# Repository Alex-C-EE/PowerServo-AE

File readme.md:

_This entire project is currently a WIP by a single person, I aim to have a High-Power (12-24V @ 10A) and a Mid Power (6-24V @ 3.6A) version completely done by the end of the year 2024._

_**Really** open to contributors._

**_It would be a REALLY bad idea to try and manufacture anything present here at this time_**

**DCServo AE**

  DCServo AE is an open-source platform designed to effortlessly transform any Brushed DC motor into a continous smart servo with **high precision** and control. Built to provide **high-torque**, **high-RPM**, and accurate positioning through absolute encoding, DCServo AE is a modular solution for hobbyists, roboticists, and makers. 
  The platform allows users to easily drop in a PowerServo AE controller onto a brushed DC motor, turning it into a powerful and precise smart servo, regardless of the motor's size or specifications.

**Project Overview**

  The platform aims to support several variations, including options for high-power, low-power, high(er)-voltage, and low-voltage setups. Each variation is designed to accommodate different performance requirements while maintaining the core features of precise motion control and absolute position feedback. All variations will be based around the **STM32G0** series of microcontrollers due to their **low cost** and **powerful timers and peripherals**. Additionally, all versions will likely use **DRV-series drivers** to ensure robust motor control.

**Core Features**
- Plug and Play: With minimal considerations for design, it is ready to be strapped on the back of any **extended or dual axis/shaft, with magnet** BRUSHED DC Motor and turn it into a Smart Servo Motor.
- Absolute Encoder: PowerServo AE uses magnetic absolute encoders for precise positioning and reliable feedback, eliminating the need for homing or recalibration after power loss.
- Modular Design: Multiple configurations allow for flexibility across a wide range of applications, from lightweight robotics to heavy-duty industrial tasks.
- Open-Source: Both hardware and software are fully open-source, allowing anyone to contribute, modify, and improve the platform.
- Compact Size: The designs are optimized for compactness, with some controllers as small as 12 mm in diameter, making them suitable for space-constrained applications.

**Getting Started**

Clone the Repository:

``git clone https://github.com/Alex-C-EE/DCServo-AE.git``

**Build Your Own:**

- Design files (PCB, schematics) are provided in each version's hardware directory. Design files are in KiCad 8.0 format.
- Code (C, STM32) is provided in each version's software directory.
- GERBERS and BOMs are also provided ready to upload to JLCPCB.

**Documentation**

_WIP, planned control: CAN, UART, PWM_

**Contributing**

We welcome contributions to the PowerServo AE project! Whether you want to improve the hardware, add new features to the firmware, or suggest new variations, feel free to contribute through:

- Issues and Pull Requests on GitHub
- Community discussions in our Discord channel

**License**
- Hardware: Licensed under the CERN Open Hardware License.
- Software: Licensed under the MIT License.

**Join the Community**

_WIP_
Stay updated with the latest developments, tutorials, and community projects:

- Follow on Hackaday.io
- Join the discussion on Discord
- Watch video tutorials and project demos on YouTube

**Similar Projects (and source of inspiration)**

Mechaduino: Similar, but for Steppers specifically
https://hackaday.io/project/11224-mechaduino

MotCTRL: Similar, but for Brushless specifically
https://github.com/osannolik/MotCtrl

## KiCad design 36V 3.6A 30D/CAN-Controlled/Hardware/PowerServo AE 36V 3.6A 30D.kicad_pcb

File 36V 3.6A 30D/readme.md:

**TODO:**
- Ensure wider free area around mounting hole between CAN and XT30
- Open Solder Jumper for CAN
- Flip XT30 Gender Wise
- Round notch corners
- U2, C7, C8 orientation
- Pull Boot0 to ground (10k)
- Switch to DRV8521A
- Mousebite between data-line
  
**REMINDER**
- DO NOT USE FEROMAGNETIC STAND-OFF NEAR A SPINNING MAGNET AND A MAGNETOMETER

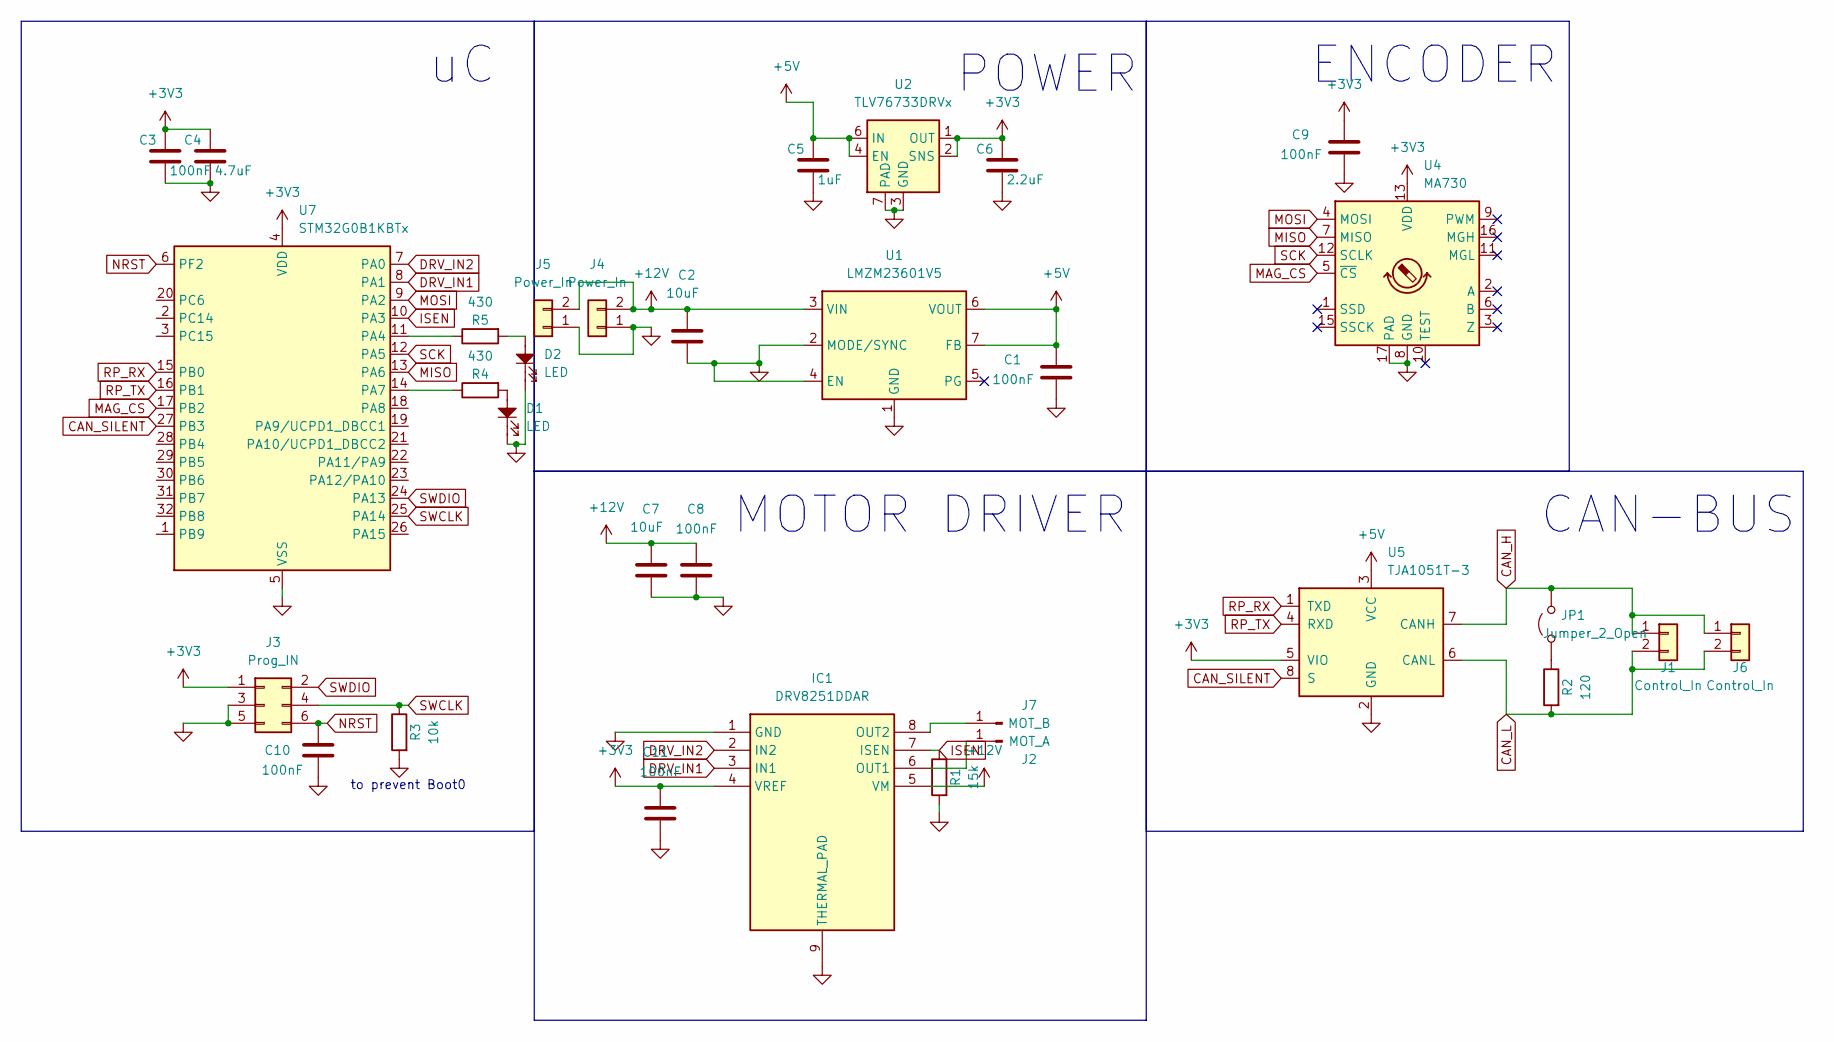
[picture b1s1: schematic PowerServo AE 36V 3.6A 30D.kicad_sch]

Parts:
C1, C3, C9, C10: 100nF; C_0402_1005Metric
C2, C7: 10uF; C_1206_3216Metric
C4: 4.7uF; C_0402_1005Metric
C5: 1uF; C_0402_1005Metric
C6: 2.2uF; C_0402_1005Metric
C8, C11: 100nF; C_0603_1608Metric
D1, D2: LED; LED_0402_1005Metric
IC1: DRV8251DDAR; SOIC127P600X170-9N; Mouser Part Number 595-DRV8251DDAR
J1, J6: Control_In; JST_XH_B2B-XH-A_1x02_P2.50mm_Vertical
J2: MOT_A; SolderWire-1sqmm_1x01_D1.4mm_OD2.7mm
J3: Prog_IN; PinHeader_2x03_P1.27mm_Vertical
J4, J5: Power_In; AMASS_XT30UPB-M_1x02_P5.0mm_Vertical
J7: MOT_B; SolderWire-1sqmm_1x01_D1.4mm_OD2.7mm
JP1: Jumper_2_Open; SolderJumper-2_P1.3mm_Open_Pad1.0x1.5mm
R1: 15k; R_0402_1005Metric
R2: 120; C_0402_1005Metric
R3: 10k; R_0402_1005Metric
R4, R5: 430; R_0402_1005Metric
U1: LMZM23601V5; Texas_SIL0010A_MicroSiP-10-1EP_3.8x3mm_P0.6mm_EP0.7x2.9mm_T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
U2: TLV76733DRVx; WSON-6-1EP_2x2mm_P0.65mm_EP1x1.6mm_ThermalVias
U4: MA730; QFN-16-1EP_3x3mm_P0.5mm_EP1.75x1.75mm
U5: TJA1051T-3; SOIC-8_3.9x4.9mm_P1.27mm
U7: STM32G0B1KBTx; LQFP-32_7x7mm_P0.8mm

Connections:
+3V3: C3.1, C4.1, C6.1, C9.2, C11.2, IC1.4 (VREF), J3.1, U2.1 (OUT), U2.2 (SNS), U4.13 (VDD), U5.5 (VIO), U7.4 (VDD)
+5V: C1.2, C5.1, U1.6 (VOUT), U1.7 (FB), U2.4 (EN), U2.6 (IN), U5.3 (VCC)
+12V: C2.2, C7.2, C8.2, IC1.5 (VM), J4.2, J5.2, U1.3 (VIN)
CAN_H: J1.1, J6.1, JP1.2 (B), U5.7 (CANH)
CAN_L: J1.2, J6.2, R2.2, U5.6 (CANL)
CAN_SILENT: U5.8 (S), U7.27 (PB3)
DRV_IN1: IC1.3 (IN1), U7.8 (PA1)
DRV_IN2: IC1.2 (IN2), U7.7 (PA0)
GND: C1.1, C2.1, C3.2, C4.2, C5.2, C6.2, C7.1, C8.1, C9.1, C10.1, C11.1, D1.1, D2.1, IC1.1 (GND), IC1.9 (THERMAL_PAD), J3.3, J3.5, J4.1, J5.1, R1.2, R3.2, U1.1 (GND), U1.2 (MODE/SYNC), U1.4 (EN), U1.11 (GND), U2.3 (GND), U2.5 (GND), U2.7 (PAD), U4.8 (GND), U4.17 (PAD), U5.2 (GND), U7.5 (VSS)
ISEN: IC1.7 (ISEN), R1.1, U7.10 (PA3)
MAG_CS: U4.5 (~CS), U7.17 (PB2)
MISO: U4.7 (MISO), U7.13 (PA6)
MOSI: U4.4 (MOSI), U7.9 (PA2)
NRST: C10.2, J3.6, U7.6 (PF2)
unnamed: D1.2, R4.2
unnamed: D2.2, R5.2
unnamed: IC1.6 (OUT1), J2.1
unnamed: IC1.8 (OUT2), J7.1
unnamed: JP1.1 (A), R2.1
unnamed: R5.1, U7.11 (PA4)
unnamed: R4.1, U7.14 (PA7)
RP_RX: U5.1 (TXD), U7.15 (PB0)
RP_TX: U5.4 (RXD), U7.16 (PB1)
SCK: U4.12 (SCLK), U7.12 (PA5)
SWCLK: J3.4, R3.1, U7.25 (PA14)
SWDIO: J3.2, U7.24 (PA13)

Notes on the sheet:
CAN-BUS
to prevent Boot0
POWER
ENCODER
MOTOR DRIVER

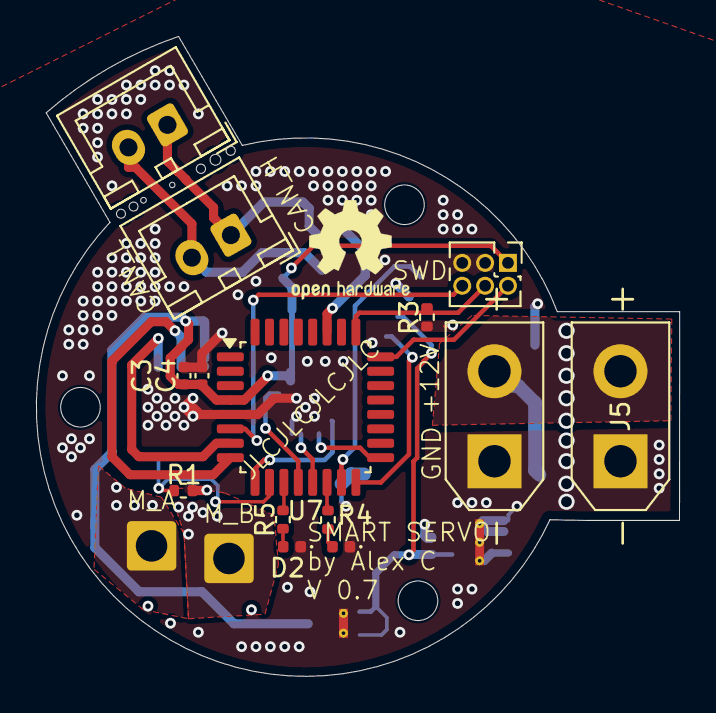
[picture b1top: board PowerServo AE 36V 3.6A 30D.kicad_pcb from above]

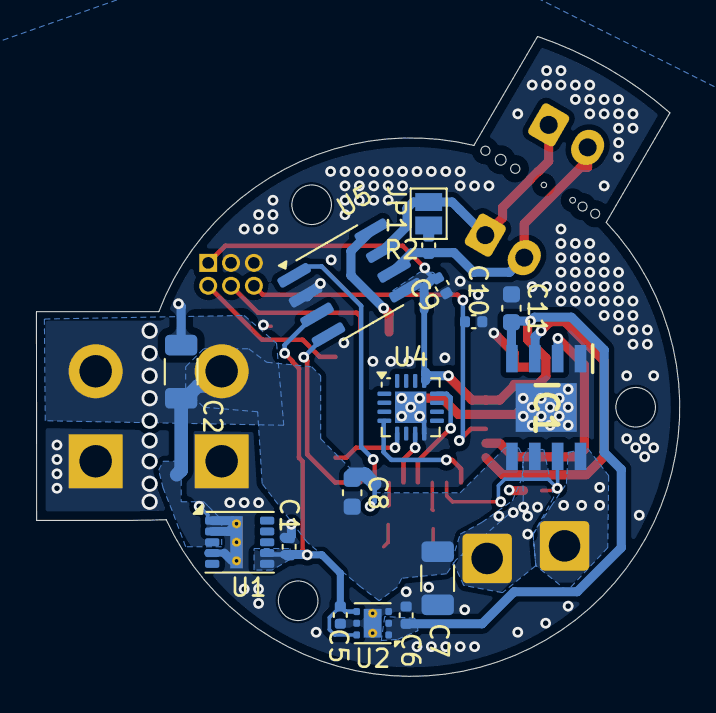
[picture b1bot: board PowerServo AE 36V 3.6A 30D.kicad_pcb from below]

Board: 4 copper layers, 35.7 x 35.5 mm, 32 parts (16 on the bottom side), 26 nets.

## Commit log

2024-10-13 CERN License
2024-10-13 Rename cern_ohl_p_v2.pdf to CERN Open-Hardware License
2024-10-13 Initial Commit Basically
2024-10-13 Added STM32CubeIDE Project
2024-10-13 Added similar projects
2024-10-13 Clarified use of STM and DRV
2024-10-13 Review Request Files and Preparations
2024-10-13 Update readme.md, wording
2024-10-13 CAD Stuff
2024-10-13 Fixed U2 / C7 Orientation
2024-10-13 Bumped to V0.7
    Following Reddit Review:
    - Added C10 as NRST Cap
    - Added R3 as Boot0/SWCLK Pull-Down
    - Added Solder Jumper for CAN Termination
    -- Downscaled R2
    - Fixed some of the odd orientations of components
2024-10-14 Rename CERN Open-Hardware License to CERN Open-Hardware License.pdf
2024-10-14 I forgor
2024-10-16 STM32 Code Update
    Motor_Control Module kinda done -> TODO: ADC read via DMA
2024-10-16 Finalized Reddit TODO
2024-10-16 idem
2024-10-17 Just some code changes
2024-10-17 Dev Version for Tests
2024-10-17 Flowcharts
2024-10-18 Documentation
2024-10-18 Draw.IO Update
2024-10-18 Flow
2024-10-21 Flowchart update. PCB Update to include 2nd XT30
2024-10-23 Starting High Power Hardware while I wait for PCBs to arrive
2024-10-23 Solved DRC
2024-10-23 Exports
